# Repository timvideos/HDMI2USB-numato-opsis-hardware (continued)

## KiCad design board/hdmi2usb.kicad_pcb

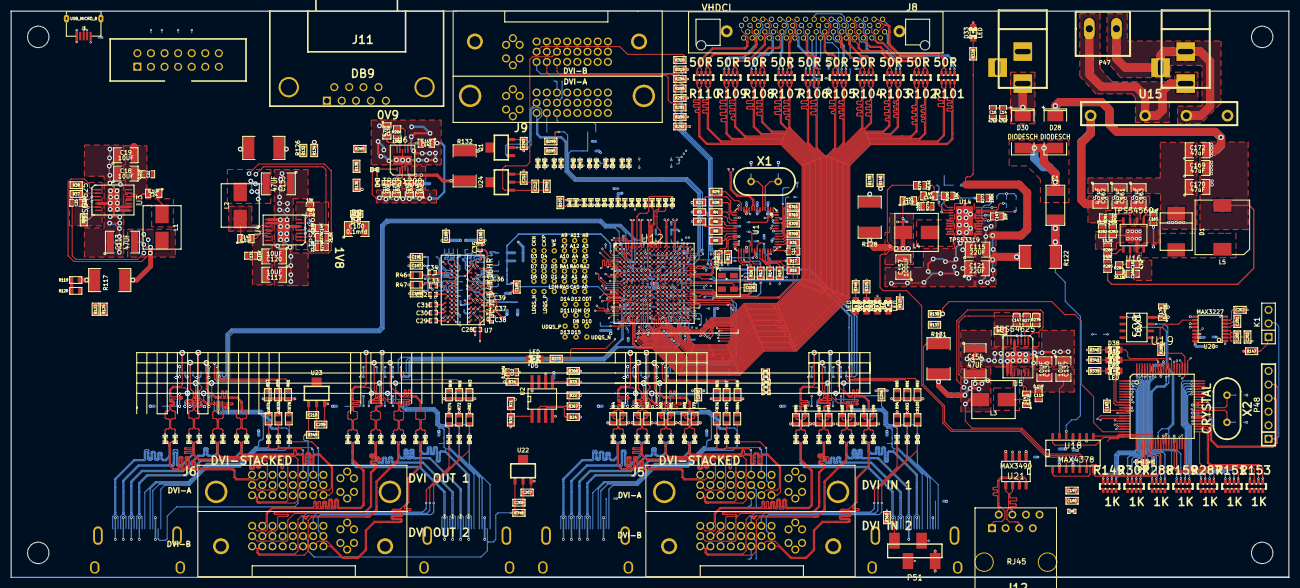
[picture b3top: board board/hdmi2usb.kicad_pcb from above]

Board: 10 copper layers, 239.0 x 105.9 mm, 688 parts (0 on the bottom side), 549 nets.

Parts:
1PIN1, 1PIN2, 1PIN3, 1PIN4: P***; MH-4MM
C1, C2, C3, C4: 0.1uFD; SM0603_Capa
C5, C6, C9, C10, C26: 0.1MFD; SM0603_Capa
C7, C8: 12pF; SM0603_Capa
C11: 47nf; SM0603_Capa
C12, C194: 0.1mfd; SM0603_Capa
C13, C15, C161, C162, C163: 4.7uF; SM1210
C14, C16: 47UF; SM0603_Capa
C17, C18, C19, C20, C116, C117, C120, C122, C125, C129, C130, C137: 10UF; SM1210
C21, C124, C133, C143: 1UF; SM0603_Capa
C22, C25, C119, C131, C144, C145, C147: 0.1UF; SM0603_Capa
C23, C132, C136: 8.2NF; SM0805
C24, C140, C141, C142, C151: 0.1UF; SM0805
C27, C48, C49, C50, C52, C53, C54, C55, C56, C58, C59, C60, C61, C62, C64, C65, C66, C67, C68, C69, C70, C71, C73, C74, C76, C77, C79, C80, C82, C83, C84, C85, C86, C87, C88, C89, C90, C91, C92, C93, C94, C95, C96, C97, C98, C99, C101, C102, C103, C104, C105, C106, C107, C108, C111, C112, C178, C181, C198: 0.1mfd; SM0402_c
C28, C29, C30, C31, C32, C33, C34, C35, C36, C37, C38, C39, C40, C41, C42, C43: 0.1mfd; SM0402_r
C44, C45, C46, C47: 1mfd; SM0603_Capa
C100: 0.1mfd; SM1210
C109: 15pf; SM0603
C110, C175, C179, C180, C182, C183, C184, C185, C186, C187, C188, C189, C190, C191, C192, C193, C195, C196, C197, C199, C200, C201, C202, C203, C204, C205, C206, C208, C210, C212: 0.1mfd; SM0603
C113, C114, C150, C153, C154, C156: 47UF; SM1812
C115, C121, C128, C134: 22UF; SM1210
C118, C123, C126, C127, C146, C148, C152, C155, C158: 10UF; SM0805
C135: 4.7UF; SM0603_Capa
C138: 0.001UF; SM0402_c
C139: 4.7UF; SM0805
C149: 1NF; SM0805
C157, C159, C160: 100UF; SM1210
C164: 2.2uF; SM1210
C165: 0.1uF; SM0603_Capa
C166: 6.2nF; SM0603_Capa
C167: 4.7uF; SM0603_Capa
C168, C169, C170, C171, C172: 47uF; SM1210
C173, C174: 0.1mfd; SM0805
C176, C177: 22pf; SM0603
C207, C209, C211: 0.33mfd; SM0603
CON1, CON2: BARREL_JACK
D1: DIODE; B560C-SMC
D2, D3, D4, D5, D32, D33, D37, D38, D39: LED; LED-0805
D28, D29, D30, D31: DIODESCH; SM2512
F1: FUSE; 1812L260THDR
GS1, GS2: GS2
J1: USB_MICRO_B; MICRO_USB_B
J2, J3, J4, J7: HDMI; HDMI_TH
J5, J6, J9: DVI-STACKED; dvi-24+5stacked
J8: VHDCI; vhdci-68
J11: DB9; DB9FC
J12: RJ45; RJ45_8
K1: CONN_3; PIN_ARRAY_3X1
L1, L2, L3: 1.5UH; IND202
L4: 2.2UH; IND202
L5: 7.2uH; Power_Inductor
P1: CONN_7X2; pin_array_7x2
P2, P3, P4, P5, P6, P7, P8, P9, P10, P11, P12, P13, P14, P15, P16, P17, P18, P19, P20, P21, P22, P23, P24, P25, P26, P27, P28, P29, P30, P31, P32, P33, P34, P35, P36, P37, P38, P39, P40, P41, P42, P43, P44, P45, P46: CONN_1; testpoint
P47: CONN_2; ScrewTerm2
P48: CONN_6; PIN_ARRAY-6X1
P51: CONN_4; PIN_ARRAY_4x1_SMD
Q1: NPN; μA78L00
R1, R2, R3, R18, R19, R20, R24, R30, R31, R34, R35, R42, R111, R133, R138, R147, R265, R292, R297, R299, R319, R324, R335, R337, R338, R344, R347, R360, R361, R362, R367, R368, R369: 10K; SM0603
R4, R5, R6, R7, R8, R9, R10, R11, R12, R13, R14, R15, R16, R17, R25, R26, R27, R29: 75R; SM0603
R21, R22, R33, R58, R60, R62, R64, R79, R81, R83, R85, R86, R87, R88, R89, R95, R97, R98, R99, R173: 50R; SM0603
R23, R28, R112, R140, R290, R293, R294, R295, R304, R328, R339, R340, R341: 2.2K; SM0603
R32, R36, R43, R57, R63, R65, R90, R348, R349, R359: 100K; SM0603
R37: 21.5K; SM0603
R38: 22.1K; SM0603
R39, R280: 10K; SM0603_Resistor
R40, R266, R272, R273, R274: 100K; SM0603_Resistor
R41: 10K; SM0402_r
R44, R45: 20K; SM0603
R46, R50, R113, R139, R141, R142, R143, R308, R310, R311, R312, R350, R351, R352, R353, R354, R355, R356, R357, R358: 100R; SM0603
R47, R49, R114, R116, R120, R134, R136, R329: 4.7K; SM0603
R48, R52, R54: 49.9R; RES_NET4
R51, R53, R55, R56, R174, R175, R176: 49.9R; SM0603
R59, R61, R66, R67, R68, R69, R91, R92, R119: 47K; SM0603
R70, R71, R72, R74, R75, R76, R93, R94, R325, R345, R346: 1.5K; SM0603
R73, R77, R80, R96: 27K; SM0603
R78, R82, R84, R100: 15K; SM0603
R101, R102, R103, R104, R105, R106, R107, R108, R109, R110: 50R; RES_NET4
R115, R137, R314, R342, R343, R370: 1K; SM0603
R117, R118, R125, R126, R127, R128, R129, R130, R131, R132: 0.03E; SM2512_N
R121, R122: 0.008E; SM2512_N
R123: 21K; SM0603
R124: 5.7K; SM0603
R135: 3.3K; SM0603
R144, R145, R146, R148, R150, R152, R154, R155, R156, R157, R158, R160, R161, R162, R163, R164, R165, R166, R167, R168, R169, R170, R171, R172, R177, R178, R179, R180, R181, R182, R183, R184, R185, R186, R187, R188, R189, R190, R191, R192, R193, R194, R195, R196, R197, R198, R199, R200, R201, R202, R203, R204, R205, R206, R207, R208, R209, R210, R211, R212, R213, R214, R215, R216, R217, R218, R219, R220, R221, R222, R223, R224, R225, R226, R227, R228, R229, R230, R231, R232, R233, R234, R235, R236, R237, R238, R239, R240, R241, R242, R243, R244, R245, R246, R247, R248, R249, R250, R251, R252, R253, R254, R255, R256, R257, R258, R259, R260, R261, R262, R263, R264, R326, R327, R331, R332, R333, R334, R336, R363: 0R; SM0402_r
R149, R151, R153, R159, R287, R288, R307: 1K; RES_NET4
R267: 200K; SM0603_Resistor
R268: 86.6K; SM0603_Resistor
R269: 1K; SM0603_Resistor
R270: 205K; SM0603_Resistor
R271: ?; SM0603_Resistor
R275: 21.5K; SM0603_Resistor
R276, R278: 22.1K; SM0603_Resistor
R277: 12.7K; SM0603_Resistor
R279: 46.4K; SM0603_Resistor
R281: 442K; SM0603_Resistor
R282: 92.3K; SM0603_Resistor
R283: 243K; SM0603_Resistor
R284: 30.1K; SM0603_Resistor
R285: 143K; SM0603_Resistor
R286: 10.2K; SM0603_Resistor
R289, R309, R313: 330R; SM0603
R291, R296, R298, R318, R323: 5.6K; SM0603
R300, R301, R302, R303, R305, R306, R315, R316, R317, R320, R321, R322: 50R; SM0402_r
R330: 0R; SM0402
U1: CY7C68013A; QFN56
U2: M25P16; SO8E_N
U3, U4, U5: TPS54625; PDSO_G14
U6: TPS51200; SON_10
U7: MT47H64M16HR; BGA84
U8, U9, U10, U11: IP4776CZ38; SSOP38
U12: SPARTAN6LXXXX-CSG324; CSG324
U13: FXO-HC536R
U14: TPS53319; DQP-22
U15: GBU15005-G; GBJ15005
U16: TPS54560
U17: MAX4377; SO8
U18: MAX4378; SO14N
U19: PIC18F85J94; TQFP-80
U20: MAX3227; SSOP17
U21: MAX3490; SO8E
U22, U23, U24: ΜA78L00; μA78L00
X1, X2: CRYSTAL; HC-49V

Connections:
/CY7C68013A/CYPRESS-RESET: C11.1, D38.2, R32.1, U1.42, U12.N14, U19.67
/CY7C68013A/DONE: R115.2, R313.2, U12.V17, U19.61
/CY7C68013A/D_N: J1.2, U1.9
/CY7C68013A/D_P: J1.3, U1.8
/CY7C68013A/INIT_B: R116.1, R289.2, U12.U3, U19.62
/CY7C68013A/PIC-OSC1: GS1.1, U1.54
/CY7C68013A/PROG_B: D39.2, R114.1, R309.2, U12.V2, U19.72
/CY7C68013A/TCK: R142.2, R312.2, U12.A17, U19.64
/CY7C68013A/TDO-USB/TDI-FPGA: R310.2, R336.2, R358.2, R363.2, U19.65
/CY7C68013A/TMS: R141.2, R311.2, U12.B18, U19.63
/CY7C68013A/U1-FD0: R4.2, U12.K12
/CY7C68013A/U1-FD1: R5.2, U12.K13
/CY7C68013A/U1-FD2: R6.2, U12.K14
/CY7C68013A/U1-FD3: R7.2, U12.J13
/CY7C68013A/U1-FD4: R8.2, U12.K16
/CY7C68013A/U1-FD5: R9.2, U12.K17
/CY7C68013A/U1-FD6: R10.2, U12.K18
/CY7C68013A/U1-FD7: R11.2, U12.L12
/CY7C68013A/U1-FIFOAD0: R14.2, U12.L13
/CY7C68013A/U1-FIFOAD1: R15.2, U12.L14
/CY7C68013A/U1-FLAGA: R27.2, U12.P16
/CY7C68013A/U1-FLAGB: R26.2, U12.L17
/CY7C68013A/U1-FLAGC: R25.2, U12.L18
/CY7C68013A/U1-IFCLK: R29.1, U12.P15
/CY7C68013A/U1-INT0#: R12.2, U12.M14
/CY7C68013A/U1-PKTEND: R16.2, U12.M16
/CY7C68013A/U1-SCL: R23.1, U1.15
/CY7C68013A/U1-SDA: R28.1, U1.16
/CY7C68013A/U1-SLCS: R17.2, U12.M18
/CY7C68013A/U1-SLRD: R20.2, U1.1, U12.J18
/CY7C68013A/U1-SLWR: R19.2, U1.2, U12.M13
/MT47H64M16HR/DDR-A0: P35.1, R175.2, U7.M8, U12.J7
/MT47H64M16HR/DDR-A1: P34.1, R174.2, U7.M3, U12.J6
/MT47H64M16HR/DDR-A2: P33.1, R176.2, U7.M7, U12.H5
/MT47H64M16HR/DDR-A3: P32.1, R52.5, U7.N2, U12.L7
/MT47H64M16HR/DDR-A4: P31.1, R48.1, U7.N8, U12.F3
/MT47H64M16HR/DDR-A5: P30.1, R52.1, U7.N3, U12.H4
/MT47H64M16HR/DDR-A6: P29.1, R48.7, U7.N7, U12.H3
/MT47H64M16HR/DDR-A7: P28.1, R52.7, U7.P2, U12.H6
/MT47H64M16HR/DDR-A8: P27.1, R48.3, U7.P8, U12.D2
/MT47H64M16HR/DDR-A9: P26.1, R52.3, U7.P3, U12.D1
/MT47H64M16HR/DDR-A10: P25.1, R53.2, U7.M2, U12.F4
/MT47H64M16HR/DDR-A11: P24.1, R48.5, U7.P7, U12.D3
/MT47H64M16HR/DDR-A12: P23.1, R51.2, U7.R2, U12.G6
/MT47H64M16HR/DDR-BA0: P22.1, R54.4, U7.L2, U12.F2
/MT47H64M16HR/DDR-BA1: P37.1, R54.8, U7.L3, U12.F1
/MT47H64M16HR/DDR-BA2: P39.1, R54.6, U7.L1, U12.E1
/MT47H64M16HR/DDR-CAS: P42.1, R55.1, U7.L7, U12.K5
/MT47H64M16HR/DDR-CKE: P38.1, R49.1, U7.K2, U12.H7
/MT47H64M16HR/DDR-CK_N: P36.1, R50.1, U7.K8, U12.G1
/MT47H64M16HR/DDR-CK_P: P21.1, R50.2, U7.J8, U12.G3
/MT47H64M16HR/DDR-D0: P17.1, U7.G8, U12.L2
/MT47H64M16HR/DDR-D1: P16.1, U7.G2, U12.L1
/MT47H64M16HR/DDR-D2: P15.1, U7.H7, U12.K2
/MT47H64M16HR/DDR-D3: P14.1, U7.H3, U12.K1
/MT47H64M16HR/DDR-D4: P13.1, U7.H1, U12.H2
/MT47H64M16HR/DDR-D5: P12.1, U7.H9, U12.H1
/MT47H64M16HR/DDR-D6: P11.1, U7.F1, U12.J3
/MT47H64M16HR/DDR-D7: P10.1, U7.F9, U12.J1
/MT47H64M16HR/DDR-D8: P9.1, U7.C8, U12.M3
/MT47H64M16HR/DDR-D9: P8.1, U7.C2, U12.M1
/MT47H64M16HR/DDR-D10: P7.1, U7.D7, U12.N2
/MT47H64M16HR/DDR-D11: P6.1, U7.D3, U12.N1
/MT47H64M16HR/DDR-D12: P5.1, U7.D1, U12.T2
/MT47H64M16HR/DDR-D13: P4.1, U7.D9, U12.T1
/MT47H64M16HR/DDR-D14: P3.1, U7.B1, U12.U2
/MT47H64M16HR/DDR-D15: P2.1, U7.B9, U12.U1
/MT47H64M16HR/DDR-LDM: P19.1, U7.F3, U12.K3
/MT47H64M16HR/DDR-LDQS_N: P44.1, U7.E8, U12.L3
/MT47H64M16HR/DDR-LDQS_P: P46.1, U7.F7, U12.L4
/MT47H64M16HR/DDR-ODT: P18.1, R47.1, U7.K9, U12.K6
/MT47H64M16HR/DDR-RAS: P41.1, R56.1, U7.K7, U12.L5
/MT47H64M16HR/DDR-UDM: P20.1, U7.B3, U12.K4
/MT47H64M16HR/DDR-UDQS_N: P45.1, U7.A8, U12.P1
/MT47H64M16HR/DDR-UDQS_P: P43.1, U7.B7, U12.P2
/MT47H64M16HR/DDR-WE: P40.1, R54.2, U7.K3, U12.E3
/expansion connectors/EXP-IO1_N: J8.35, R101.3, R101.4, U12.V5
/expansion connectors/EXP-IO1_P: J8.1, R101.1, R101.2, U12.U5
/expansion connectors/EXP-IO2_N: J8.37, R101.7, R101.8, U12.V6
/expansion connectors/EXP-IO2_P: J8.3, R101.5, R101.6, U12.T6
/expansion connectors/EXP-IO3_N: J8.38, R102.3, R102.4, U12.P7
/expansion connectors/EXP-IO3_P: J8.4, R102.1, R102.2, U12.N6
/expansion connectors/EXP-IO4_N: J8.40, R102.7, R102.8, U12.T7
/expansion connectors/EXP-IO4_P: J8.6, R102.5, R102.6, U12.R7
/expansion connectors/EXP-IO5_N: J8.41, R103.3, R103.4, U12.V7
/expansion connectors/EXP-IO5_P: J8.7, R103.1, R103.2, U12.U7
/expansion connectors/EXP-IO6_N: J8.43, R103.7, R103.8, U12.T8
/expansion connectors/EXP-IO6_P: J8.9, R103.5, R103.6, U12.R8
/expansion connectors/EXP-IO7_N: J8.44, R104.3, R104.4, U12.P8
/expansion connectors/EXP-IO7_P: J8.10, R104.1, R104.2, U12.N7
/expansion connectors/EXP-IO8_N: J8.46, R104.7, R104.8, U12.V8
/expansion connectors/EXP-IO8_P: J8.12, R104.5, R104.6, U12.U8
/expansion connectors/EXP-IO9_N: J8.47, R105.3, R105.4, U12.N8
/expansion connectors/EXP-IO9_P: J8.13, R105.1, R105.2, U12.M8
/expansion connectors/EXP-IO10_N: J8.49, R105.7, R105.8, U12.N9
/expansion connectors/EXP-IO10_P: J8.15, R105.5, R105.6, U12.M10
/expansion connectors/EXP-IO11_N: J8.54, R106.3, R106.4, U12.V10
/expansion connectors/EXP-IO11_P: J8.20, R106.1, R106.2, U12.U10
/expansion connectors/EXP-IO12_N: J8.56, R106.7, R106.8, U12.N11
/expansion connectors/EXP-IO12_P: J8.22, R106.5, R106.6, U12.M11
/expansion connectors/EXP-IO13_N: J8.57, R107.3, R107.4, U12.V11
/expansion connectors/EXP-IO13_P: J8.23, R107.1, R107.2, U12.U11
/expansion connectors/EXP-IO14_N: J8.59, R107.7, R107.8, U12.P11
/expansion connectors/EXP-IO14_P: J8.25, R107.5, R107.6, U12.N10
/expansion connectors/EXP-IO15_N: J8.60, R108.3, R108.4, U12.T11
/expansion connectors/EXP-IO15_P: J8.26, R108.1, R108.2, U12.R11
/expansion connectors/EXP-IO16_N: J8.62, R108.7, R108.8, U12.P12
/expansion connectors/EXP-IO16_P: J8.28, R108.5, R108.6, R112.2, U12.N12
/expansion connectors/EXP-IO17_N: J8.63, R109.3, R109.4, U12.T10
/expansion connectors/EXP-IO17_P: J8.29, R109.1, R109.2, U12.R10
/expansion connectors/EXP-IO18_N: J8.65, R109.7, R109.8, U12.V12
/expansion connectors/EXP-IO18_P: J8.31, R109.5, R109.6, U12.T12
/expansion connectors/EXP-IO19_N: J8.66, R110.3, R110.4, U12.V13
/expansion connectors/EXP-IO19_P: J8.32, R110.1, R110.2, U12.U13
/expansion connectors/EXP-IO20_N: J8.68, R110.7, R110.8, U12.V15
/expansion connectors/EXP-IO20_P: J8.34, R110.5, R110.6, U12.U15
/expansion connectors/GTP-RX-0_N: J9.A17, R315.2, U12.C5
/expansion connectors/GTP-RX-0_P: J9.A18, R305.2, R334.2
/expansion connectors/GTP-RX-1_N: J9.A9, R320.1, U12.C7
/expansion connectors/GTP-RX-1_P: J9.A10, R322.1, R332.2
/expansion connectors/GTP-RX-2_N: J9.A1, R301.1, U12.C11
/expansion connectors/GTP-RX-2_P: J9.A2, R303.1, U12.D11
/expansion connectors/GTP-RX-3_N: J9.A12, R321.2, U12.C13
/expansion connectors/GTP-RX-3_P: J9.A13, R317.2, R333.2
/expansion connectors/GTP-RX-CLK_N: J9.A24, R300.2, U12.A10
/expansion connectors/GTP-RX-CLK_P: J9.A23, R302.2, R331.2
/expansion connectors/GTP-RX-ECLK_N: J9.A4, R306.1, U12.C9
/expansion connectors/GTP-RX-ECLK_P: J9.A5, R316.1, U12.D9
/expansion connectors/GTP-RX-HOT: Q1.2, U12.F14
/expansion connectors/GTP-RX-SCL: R304.1, R323.1, R324.2, U12.C17
/expansion connectors/GTP-RX-SDA: R295.1, R298.1, R299.2, U12.C18
/expansion connectors/GTP-RX-VIO: J9.A8, U12.D17
/expansion connectors/GTP-RX_HOT: J9.A16, Q1.1
/expansion connectors/GTP-RX_SCL: J9.A6, R323.2
/expansion connectors/GTP-RX_SDA: J9.A7, R298.2
/expansion connectors/GTP-TX-0_N: J9.B17, U12.A6
/expansion connectors/GTP-TX-0_P: J9.B18, U12.B6
/expansion connectors/GTP-TX-1_N: J9.B9, U12.A4
/expansion connectors/GTP-TX-1_P: J9.B10, U12.B4
/expansion connectors/GTP-TX-2_N: J9.B1, U12.A12
/expansion connectors/GTP-TX-2_P: J9.B2, U12.B12
/expansion connectors/GTP-TX-3_N: J9.B12, U12.A14
/expansion connectors/GTP-TX-3_P: J9.B13, U12.B14
/expansion connectors/GTP-TX-CLK_N: J9.B24, U12.B8, U12.E18
/expansion connectors/GTP-TX-CLK_P: J9.B23, U12.A8, U12.E16
/expansion connectors/GTP-TX-ECLK_N: J9.B4, R330.2
/expansion connectors/GTP-TX-ECLK_P: J9.B5, U12.F10
/expansion connectors/GTP-TX-HOT: R318.1, R319.2, U12.H17
/expansion connectors/GTP-TX-SCL: R294.1, R296.1, R297.2, U12.G13
/expansion connectors/GTP-TX-SDA: R290.1, R291.1, R292.2, U12.G14
/expansion connectors/GTP-TX-VCC5V0: C212.1, J9.B14, R359.2, U24.1
/expansion connectors/GTP-TX-VIO: J9.B8, U12.G18
/expansion connectors/GTP-TX_HOT: J9.B16, R318.2
/expansion connectors/GTP-TX_SCL: J9.B6, R296.2
/expansion connectors/GTP-TX_SDA: J9.B7, R291.2
/expansion connectors/TDO-FPGA/TDO-JTAG: R143.2, R308.2, U12.D16, U19.66
/hdmi/HDMI-TX1-VCC5V0: C208.1, J3.18, J6.B14, R348.1, U22.1
/hdmi/HDMI-TX2-VCC5V0: C210.1, J2.18, J6.A14, R349.1, U23.1
/hdmi/P1-CEC: J4.13, R80.2, U10.23
/hdmi/P1-HOT: C205.2, R84.2, R187.1, R205.1, R342.2, U10.20
/hdmi/P1-SCL: R76.2, R185.1, R201.1, U10.22
/hdmi/P1-SDA: R75.2, R186.1, R202.1, U10.21
/hdmi/P2-CEC: J3.13, R77.2, U9.23
/hdmi/P2-HOT: R82.2, R198.1, R216.1, U9.20
/hdmi/P2-SCL: R74.2, R196.1, R212.1, U9.22
/hdmi/P2-SDA: R72.2, R197.1, R213.1, U9.21
/hdmi/P3-CEC: J7.13, R96.2, U11.23
/hdmi/P3-HOT: C206.2, R100.2, R227.1, R242.1, R343.2, U11.20
/hdmi/P3-SCL: R94.2, R223.1, R240.1, U11.22
/hdmi/P3-SDA: R93.2, R224.1, R241.1, U11.21
/hdmi/P4-CEC: J2.13, R73.2, U8.23
/hdmi/P4-HOT: R78.2, R249.1, R264.1, U8.20
/hdmi/P4-SCL: R71.2, R245.1, R262.1, U8.22
/hdmi/P4-SDA: R70.2, R246.1, R263.1, U8.21
/hdmi/TMDS-RX1-0_N: R81.1, R182.1, R206.1, U10.27, U12.T18
/hdmi/TMDS-RX1-0_P: R60.1, R181.1, R207.1, U10.10, U12.T17
/hdmi/TMDS-RX1-1_N: R83.1, R180.1, R203.1, U10.30, U12.N16
/hdmi/TMDS-RX1-1_P: R62.1, R179.1, R204.1, U10.7, U12.N15
/hdmi/TMDS-RX1-2_N: R85.1, R178.1, R199.1, U10.33, U12.U18
/hdmi/TMDS-RX1-2_P: R64.1, R177.1, R200.1, U10.4, U12.U17
/hdmi/TMDS-RX1-CEC: R65.2, U10.16, U12.P18
/hdmi/TMDS-RX1-CLK_N: R79.1, R184.1, R209.1, U10.24, U12.L16
/hdmi/TMDS-RX1-CLK_P: R58.1, R183.1, R208.1, U10.13, U12.L15
/hdmi/TMDS-RX1-HOT: U10.19, U12.N18
/hdmi/TMDS-RX1-SCL: R67.2, U10.17, U12.N17
/hdmi/TMDS-RX1-SDA: R69.2, U10.18, U12.P17
/hdmi/TMDS-RX2-0_N: R98.2, R228.1, R237.1, U11.27, U12.F18
/hdmi/TMDS-RX2-0_P: R88.1, R229.1, R236.1, U11.10, U12.F17
/hdmi/TMDS-RX2-1_N: R97.2, R225.1, R235.1, U11.30, U12.F16
/hdmi/TMDS-RX2-1_P: R87.1, R226.1, R234.1, U11.7, U12.F15
/hdmi/TMDS-RX2-2_N: R95.2, R221.1, R233.1, U11.33, U12.H14
/hdmi/TMDS-RX2-2_P: R86.1, R222.1, R232.1, U11.4, U12.H13
/hdmi/TMDS-RX2-CEC: R90.2, U11.16, U12.G16
/hdmi/TMDS-RX2-CLK_N: R99.2, R231.1, R239.1, U11.24, U12.H16
/hdmi/TMDS-RX2-CLK_P: R89.1, R230.1, R238.1, U11.13, U12.H15
/hdmi/TMDS-RX2-HOT: U11.19, U12.D18
/hdmi/TMDS-RX2-SCL: R91.2, U11.17, U12.H18
/hdmi/TMDS-RX2-SDA: R92.2, U11.18, U12.H12
/hdmi/TMDS-TX1-0_N: R193.1, R217.1, U9.27, U12.T3
/hdmi/TMDS-TX1-0_P: R192.1, R218.1, U9.10, U12.R3
/hdmi/TMDS-TX1-1_N: R191.1, R214.1, U9.30, U12.V4
/hdmi/TMDS-TX1-1_P: R190.1, R215.1, U9.7, U12.T4
/hdmi/TMDS-TX1-2_N: R189.1, R210.1, U9.33, U12.T5
/hdmi/TMDS-TX1-2_P: R188.1, R211.1, U9.4, U12.R5
/hdmi/TMDS-TX1-CEC: R63.2, U9.16, U12.P6
/hdmi/TMDS-TX1-CLK_N: R195.1, R220.1, U9.24, U12.V9
/hdmi/TMDS-TX1-CLK_P: R194.1, R219.1, U9.13, U12.T9
/hdmi/TMDS-TX1-HOT: U9.19, U12.N5
/hdmi/TMDS-TX1-SCL: R66.2, U9.17, U12.V16
/hdmi/TMDS-TX1-SDA: R68.2, U9.18, U12.U16
/hdmi/TMDS-TX2-0_N: R250.1, R259.1, U8.27, U12.A16
/hdmi/TMDS-TX2-0_P: R251.1, R258.1, U8.10, U12.B16
/hdmi/TMDS-TX2-1_N: R247.1, R257.1, U8.30, U12.A3
/hdmi/TMDS-TX2-1_P: R248.1, R256.1, U8.7, U12.B3
/hdmi/TMDS-TX2-2_N: R243.1, R255.1, U8.33, U12.A2
/hdmi/TMDS-TX2-2_P: R244.1, R254.1, U8.4, U12.B2
/hdmi/TMDS-TX2-CEC: R57.2, U8.16, U12.E4
/hdmi/TMDS-TX2-CLK_N: R253.1, R261.1, U8.24, U12.A15
/hdmi/TMDS-TX2-CLK_P: R252.1, R260.1, U8.13, U12.C15
/hdmi/TMDS-TX2-HOT: U8.19, U12.G9
/hdmi/TMDS-TX2-SCL: R59.2, U8.17, U12.F6
/hdmi/TMDS-TX2-SDA: R61.2, U8.18, U12.F5
/pmic/232-FON: U19.8, U20.12
/pmic/232-INV: U19.10, U20.10
/pmic/232-RDY: U19.5, U20.1
/pmic/CURRENT_0V9: U17.7, U19.33
/pmic/CURRENT_1V2: U18.7, U19.30
/pmic/CURRENT_1V8: U17.1, U19.29
/pmic/CURRENT_3V3: U18.1, U19.28
/pmic/CURRENT_5V0: U18.8, U19.27
/pmic/CURRENT_12V0: U18.14, U19.22
/pmic/DDR0V9_RS+: C146.2, C148.2, C152.2, C155.2, C158.2, R127.2, R132.2, U6.3, U6.5, U17.5
/pmic/DDR1V8_RS+: C145.2, C150.2, C153.2, L2.2, R125.2, R126.2, R275.1, U4.1, U17.3
/pmic/IR-LED: R140.1, U19.54
/pmic/L-GRX-A: R149.7, U19.1
/pmic/L-GRX-D: R307.3, U19.79
/pmic/L-GRX-E: R149.5, U19.2
/pmic/L-GRX-M: R307.1, U19.80
/pmic/L-GTX-A: R151.3, U19.56
/pmic/L-GTX-D: R287.1, U19.58
/pmic/L-GTX-E: R151.5, U19.55
/pmic/L-GTX-M: R151.1, U19.57
/pmic/L-PGOOD: R287.3, U19.34
/pmic/L-RX1-A: R159.3, U19.68
/pmic/L-RX1-C: R149.1, U19.4
/pmic/L-RX1-D: R288.1, U19.76
/pmic/L-RX1-E: R151.7, U19.39
/pmic/L-RX2-A: R159.5, U19.60
/pmic/L-RX2-C: R307.5, U19.78
/pmic/L-RX2-D: R288.5, U19.74
/pmic/L-RX2-E: R153.3, U19.41
/pmic/L-TX1-A: R159.1, U19.69
/pmic/L-TX1-C: R149.3, U19.3
/pmic/L-TX1-D: R288.3, U19.75
/pmic/L-TX1-E: R153.1, U19.40
/pmic/L-TX2-A: R159.7, U19.59
/pmic/L-TX2-C: R307.7, U19.77
/pmic/L-TX2-D: R288.7, U19.73
/pmic/L-TX2-E: R153.5, U19.42
/pmic/L-V-A: R287.5, U19.35
/pmic/L-V-D: R287.7, U19.36
/pmic/L-V-E: R153.7, U19.43
/pmic/OSC1: C176.2, GS1.2, U19.49, X2.2
/pmic/OSC2: C177.2, U19.50, X2.1
/pmic/PIC-RESET: C204.1, D37.2, K1.2, P48.1, U12.T14, U19.9
/pmic/RS232RX: U19.6, U20.9
/pmic/RS232RX-IN: J11.3, U20.8
/pmic/RS232TX: U19.7, U20.11
/pmic/RS232TX-OUT: J11.2, U20.13
/pmic/RS422RX: U19.37, U21.2
/pmic/RS422RX-IN+: J12.2, U21.8
/pmic/RS422RX-IN-: J12.1, U21.7
/pmic/RS422TX: U19.38, U21.3
/pmic/RS422TX-IN+: J12.5, U21.5
/pmic/RS422TX-IN-: J12.4, U21.6
/pmic/SPI-CS-PIC: U12.V14, U19.13
/pmic/SPI-SCK: P48.5, R369.1, U2.6, U12.R15, U19.44, U19.52
/pmic/SPI-SDI: R22.1, U12.R13, U19.45
/pmic/SPI-SDO: P48.4, R33.2, U12.T13, U19.46, U19.47
/pmic/USB_DM: P51.2, U19.17
/pmic/USB_DP: P51.3, U19.16
/pmic/VCC3V3_RS+: C151.1, C157.2, C159.2, C160.2, L4.2, R128.2, R129.2, R279.2, U18.3
/pmic/VCC5V0_RS+: C25.2, C113.2, C114.2, L1.2, R37.1, R117.2, R118.2, U3.1, U18.10
/pmic/VCC12V0_RS+: F1.2, R121.2, R122.2, U18.12
/pmic/VSENSE_0V9: R139.2, U19.21
/pmic/VSENSE_1V2: R137.2, R138.1, U19.20
/pmic/VSENSE_1V8: R135.2, R136.1, U19.19
/pmic/VSENSE_3V3: R133.2, R134.1, U19.18
/pmic/VSENSE_5V0: R123.2, R124.1, U19.15
/pmic/VSENSE_12V0: R119.2, R120.1, U19.14
/power/Conference 12V: C168.2, C169.2, C170.2, C171.2, C172.2, D28.1, D29.1, L5.2, R285.2
/power/Consumer 12V: C14.2, C16.2, CON2.1, D30.1, D31.1
/power/VCC1V2_RS+: C147.1, C154.2, C156.2, L3.2, R130.2, R131.2, R137.1, R277.1, U5.1, U18.6
/power/VIN 48: C13.2, C15.2, C161.2, C162.2, C163.2, C164.2, R281.2, U15.1, U16.2
/power/VIN +48V: CON1.1, P47.2, U15.2
/power/VIN -48V: CON1.2, CON1.3, P47.1, U15.3
/spartan6/CMPCS_B_2: R314.1, U12.P13
/spartan6/GCLK: C109.1, U12.K15, U13.3
/spartan6/GND--OR--VCC1V2-1: R156.1, R157.1, U12.D10
/spartan6/GNDT-NC1: R169.1, U12.C4
/spartan6/GNDT-NC2: R170.1, U12.C6
/spartan6/GNDT-NC3: R171.1, U12.A7
/spartan6/GNDT-NC4: R172.1, U12.D8
/spartan6/GNDT-NC5: R160.1, U12.B9
/spartan6/GNDT-NC6: R161.1, U12.A9
/spartan6/GNDT-NC7: R162.1, U12.C10
/spartan6/GNDT-NC8: R163.1, U12.F9
/spartan6/GNDT-NC9: R164.1, U12.A11
/spartan6/GNDT-NC10: R165.1, U12.E13
/spartan6/GNDT-NC11: R167.1, U12.C14
/spartan6/GTP-REF: R173.1, U12.E7
/spartan6/GTP-RX-0_P--OR--GND: R158.1, R334.1, U12.D5
/spartan6/GTP-RX-1_P--OR--VCC3V3: R150.1, R332.1, U12.D7
/spartan6/GTP-RX-3_P--OR--VCC3V3: R152.1, R333.1, U12.D13
/spartan6/GTP-RX-CLK_P--OR--VCC3V3: R148.1, R331.1, U12.B10
/spartan6/GTP-TX-ECLK_N--OR--VCC3V3: R146.1, R330.1, U12.E10
/spartan6/GTP_CAL: R173.2, R326.1, R327.1, U12.E5
/spartan6/LED-DEBUG: R370.2, U12.P3
/spartan6/M0: GS2.1, R111.2, U12.T15
/spartan6/NC-VCCAUXT1: R168.1, U12.D4
/spartan6/NC-VCCAUXT2: R166.1, U12.D14
/spartan6/RZQ: R113.2, U12.L6
/spartan6/SPI-CS-FLASH: R21.1, U12.V3
/spartan6/SUSPEND: R329.2, U12.R16
/spartan6/TDO_USB/TDI-FPGA-LX: R336.1, U12.D15
/spartan6/TDO_USB/TDI-FPGA-LXT: R363.1, U12.F13
/spartan6/U1-SLOE: R13.2, U12.J16
/spartan6/VCC3V3--OR--GND1: R144.1, R145.1, U12.B5
/spartan6/VCC3V3--OR--VCC1V2: R154.1, R155.1, U12.E9
DDR0V9: C27.1, C111.1, C112.1, C184.1, C185.1, C186.1, C187.1, C188.1, C189.1, C190.1, C191.1, C192.1, C193.1, R48.2, R48.4, R48.6, R48.8, R51.1, R52.2, R52.4, R52.6, R52.8, R53.1, R54.1, R54.3, R54.5, R54.7, R55.2, R56.2, R127.1, R132.1, R139.1, R174.1, R175.1, R176.1, U12.C1, U12.M5, U12.N3, U17.6
DDR1V8: C28.1, C29.1, C30.1, C31.1, C32.1, C33.1, C34.1, C35.1, C36.1, C37.1, C38.1, C39.1, C40.1, C41.1, C42.1, C43.1, C86.1, C89.1, C92.1, C95.1, C98.1, C101.1, C118.2, C123.2, C126.1, C127.2, R41.1, R44.1, R125.1, R126.1, R135.1, U6.2, U7.A1, U7.A9, U7.C1, U7.C3, U7.C7, U7.C9, U7.E1, U7.E9, U7.G1, U7.G3, U7.G7, U7.G9, U7.J1, U7.J9, U7.M9, U7.R1, U12.E2, U12.G4, U12.J2, U12.J5, U12.M4, U12.R2, U17.2
GND: C1.2, C2.2, C3.2, C4.2, C5.2, C6.2, C7.1, C8.2, C9.2, C10.2, C11.2, C12.2, C13.1, C14.1, C15.1, C16.1, C17.2, C18.1, C19.1, C20.2, C21.1, C22.2, C23.1, C26.2, C27.2, C28.2, C29.2, C30.2, C31.2, C32.2, C33.2, C34.2, C35.2, C36.2, C37.2, C38.2, C39.2, C40.2, C41.2, C42.2, C43.2, C44.2, C45.2, C46.2, C47.2, C48.2, C49.2, C50.2, C52.2, C53.2, C54.2, C55.2, C56.2, C58.2, C59.2, C60.2, C61.2, C62.2, C64.2, C65.2, C66.2, C67.2, C68.2, C69.2, C70.2, C71.2, C73.2, C74.2, C76.2, C77.2, C79.2, C80.2, C82.2, C83.2, C84.2, C85.2, C86.2, C87.2, C88.2, C89.2, C90.2, C91.2, C92.2, C93.2, C94.2, C95.2, C96.2, C97.2, C98.2, C99.2, C100.2, C101.2, C102.2, C103.2, C104.2, C105.2, C106.2, C107.2, C108.2, C109.2, C110.2, C111.2, C112.2, C113.1, C114.1, C115.1, C116.2, C117.1, C118.1, C119.2, C120.1, C121.1, C122.2, C123.1, C124.1, C125.1, C126.2, C127.1, C128.1, C129.1, C130.1, C131.2, C132.1, C133.1, C134.1, C135.1, C136.1, C137.1, C138.2, C139.1, C142.1, C143.1, C146.1, C148.1, C150.1, C152.1, C153.1, C154.1, C155.1, C156.1, C157.1, C158.1, C159.1, C160.1, C161.1, C162.1, C163.1, C164.1, C166.2, C167.1, C168.1, C169.1, C170.1, C171.1, C172.1, C173.2, C174.2, C175.2, C176.1, C177.1, C178.2, C179.2, C180.2, C181.2, C182.2, C183.1, C184.2, C185.2, C186.2, C187.2, C188.2, C189.2, C190.2, C191.2, C192.2, C193.2, C194.2, C195.2, C196.2, C197.2, C198.2, C199.2, C202.1, C203.1, C204.2, C205.1, C206.1, CON2.2, CON2.3, D1.1, D3.2, D4.2, D5.2, D32.2, D33.2, GS2.2, J1.5, J2.2, J2.5, J2.8, J2.11, J2.17, J3.2, J3.5, J3.8, J3.11, J3.17, J4.2, J4.5, J4.8, J4.11, J4.17, J5.A3, J5.A11, J5.A15, J5.A19, J5.A22, J5.B3, J5.B11, J5.B15, J5.B19, J5.B22, J6.A3, J6.A11, J6.A15, J6.A19, J6.A22, J6.B3, J6.B11, J6.B15, J6.B19, J6.B22, J7.2, J7.5, J7.8, J7.11, J7.17, J8.2, J8.5, J8.8, J8.11, J8.14, J8.21, J8.24, J8.27, J8.30, J8.33, J8.36, J8.39, J8.42, J8.45, J8.48, J8.55, J8.58, J8.61, J8.64, J8.67, J9.A3, J9.A11, J9.A15, J9.A19, J9.A22, J9.B3, J9.B11, J9.B15, J9.B19, J9.B22, J11.5, J12.3, J12.6, K1.3, P1.1, P1.3, P1.5, P1.7, P1.9, P1.11, P1.13, P48.3, P51.1, R18.1, R38.2, R45.1, R46.2, R47.2, R49.2, R78.1, R82.1, R84.1, R100.1, R112.1, R113.1, R120.2, R124.2, R134.2, R136.2, R138.2, R145.2, R156.2, R158.2, R160.2, R161.2, R162.2, R163.2, R164.2, R165.2, R167.2, R169.2, R170.2, R171.2, R172.2, R265.2, R268.2, R270.2, R271.2, R272.1, R276.2, R278.2, R280.1, R282.2, R283.2, R286.1, R292.1, R297.1, R299.1, R319.1, R324.1, R329.1, R335.1, R337.1, R338.1, R344.1, R347.1, R360.2, R361.1, R362.1, U1.6, U1.10, U1.12, U1.14, U1.26, U1.28, U1.41, U1.53, U1.56, U2.4, U3.5, U3.8, U3.9, U3.15, U4.5, U4.8, U4.9, U4.15, U5.5, U5.8, U5.9, U5.15, U6.4, U6.8, U6.11, U7.A3, U7.A7, U7.B2, U7.B8, U7.D2, U7.D8, U7.E3, U7.E7, U7.F2, U7.F8, U7.H2, U7.H8, U7.J3, U7.J7, U7.N1, U7.P9, U8.3, U8.5, U8.8, U8.11, U8.14, U8.25, U8.28, U8.31, U8.34, U8.36, U9.3, U9.5, U9.8, U9.11, U9.14, U9.25, U9.28, U9.31, U9.34, U9.36, U10.3, U10.5, U10.8, U10.11, U10.14, U10.25, U10.28, U10.31, U10.34, U10.36, U11.3, U11.5, U11.8, U11.11, U11.14, U11.25, U11.28, U11.31, U11.34, U11.36, U12.A1, U12.A18, U12.B13, U12.C12, U12.C16, U12.E15, U12.F11, U12.G2, U12.G5, U12.G17, U12.H8, U12.H10, U12.J4, U12.J9, U12.J11, U12.J15, U12.K8, U12.K10, U12.L9, U12.L11, U12.M2, U12.M6, U12.M17, U12.N13, U12.R1, U12.R4, U12.R9, U12.R14, U12.R18, U12.T16, U12.U6, U12.U12, U12.V1, U12.V18, U13.2, U14.23, U15.4, U16.7, U16.9, U17.4, U18.11, U19.11, U19.26, U19.31, U19.51, U19.70, U20.14, U21.4
unnamed: K1.1, R147.1
unnamed: D2.2, R115.1
unnamed: R34.1, U2.7
unnamed: R21.2, R30.1, U2.1
unnamed: R24.2, U2.3
unnamed: R22.2, R367.2, U2.2
unnamed: R33.1, R368.1, U2.5
unnamed: D5.1, R370.1
unnamed: R3.2, R13.1, U1.35
unnamed: R1.2, R12.1, U1.33
unnamed: R31.2, U1.44
unnamed: R10.1, U1.24
unnamed: R310.1, U1.47
unnamed: R29.2, U1.13
unnamed: R289.1, U1.51
unnamed: R6.1, U1.20
unnamed: R7.1, U1.21
unnamed: R8.1, U1.22
unnamed: R9.1, U1.23
unnamed: R11.1, U1.25
unnamed: R4.1, U1.18
unnamed: R5.1, U1.19
unnamed: R17.1, R18.2, U1.40
unnamed: C7.2, U1.4, X1.2
unnamed: C8.1, U1.5, X1.1
unnamed: R25.1, U1.31
unnamed: R26.1, U1.30
unnamed: R27.1, U1.29
unnamed: R344.2, R346.2, U1.36
unnamed: R14.1, U1.37
unnamed: R16.1, U1.39
unnamed: J1.1, R347.2
unnamed: R308.1, U1.45
unnamed: R311.1, U1.48
unnamed: R312.1, U1.49
unnamed: R309.1, U1.46
unnamed: R313.1, U1.52
unnamed: D3.1, R345.1
unnamed: D4.1, R346.1
unnamed: R2.2, R345.2, U1.34
unnamed: R325.1, U1.50
unnamed: D32.1, R325.2
unnamed: R15.1, U1.38
unnamed: C26.1, R44.2, R45.2, U7.J2
unnamed: R46.1, U7.L8
unnamed: R269.1, U14.2
unnamed: R267.2, R268.1, R269.2
unnamed: C24.1, L1.1, U3.10, U3.11
unnamed: C24.2, U3.12
unnamed: R271.1, U14.22
unnamed: R270.1, U14.21
unnamed: C144.1, U14.4
unnamed: R272.2, U14.20
unnamed: R273.2, U14.3
unnamed: C143.2, R273.1, U14.18
unnamed: C144.2, L4.1, R274.2, U14.6, U14.7, U14.8, U14.9, U14.10, U14.11
unnamed: R266.1, U6.9
unnamed: C149.1, R279.1, R280.2, U14.1
unnamed: C138.1, R41.2, R265.1, U6.1
unnamed: C142.2, U6.6
unnamed: D28.2, D29.2, D30.2, D31.2, F1.1
unnamed: D33.1, R328.2
unnamed: C25.1, R37.2, R38.1, U3.2
unnamed: R35.2, U3.7
unnamed: R36.2, U3.6
unnamed: C23.2, U3.4
unnamed: C166.1, R284.1
unnamed: R285.1, R286.2, U16.5
unnamed: C165.2, D1.2, L5.1, U16.8
unnamed: C165.1, U16.1
unnamed: R283.1, U16.4
unnamed: R281.1, R282.1, U16.3
unnamed: C149.2, C151.2, R274.1
unnamed: C21.2, R36.1, U3.3
unnamed: C141.2, U5.12
unnamed: C141.1, L3.1, U5.10, U5.11
unnamed: C136.2, U5.4
unnamed: C147.2, R277.2, R278.1, U5.2
unnamed: C133.2, R43.1, U5.3
unnamed: R43.2, U5.6
unnamed: C140.2, U4.12
unnamed: C140.1, L2.1, U4.10, U4.11
unnamed: C132.2, U4.4
unnamed: C124.2, R40.1, U4.3
unnamed: R40.2, U4.6
unnamed: R39.2, U4.7
unnamed: R42.2, U5.7
unnamed: C145.1, R275.2, R276.1, U4.2
unnamed: C167.2, R284.2, U16.6
unnamed: J5.B14, R362.2
unnamed: J4.18, R337.2
unnamed: J5.A14, R361.2
unnamed: C46.1, U9.37
unnamed: C209.2, C210.2, R349.2, U23.2
unnamed: C207.2, C208.2, R348.2, U22.2
unnamed: J2.1, R254.2
unnamed: J2.9, R259.2
unnamed: J2.7, R258.2
unnamed: J2.6, R257.2
unnamed: J2.4, R256.2
unnamed: J2.3, R255.2
unnamed: J2.10, R260.2
unnamed: J7.19, R242.2
unnamed: J7.16, R241.2
unnamed: J7.15, R240.2
unnamed: J7.12, R239.2
unnamed: J7.10, R238.2
unnamed: J7.9, R237.2
unnamed: J2.19, R264.2
unnamed: J2.16, R263.2
unnamed: J2.15, R262.2
unnamed: J2.12, R261.2
unnamed: J3.19, R198.2
unnamed: J4.7, R181.2
unnamed: J4.6, R180.2
unnamed: J4.4, R179.2
unnamed: J4.3, R178.2
unnamed: J4.1, R177.2
unnamed: J4.9, R182.2
unnamed: J3.16, R197.2
unnamed: J3.15, R196.2
unnamed: J3.12, R195.2
unnamed: J3.10, R194.2
unnamed: J3.9, R193.2
unnamed: J7.7, R236.2
unnamed: J7.6, R235.2
unnamed: J7.4, R234.2
unnamed: J7.3, R233.2
unnamed: J7.1, R232.2
unnamed: J4.19, R187.2
unnamed: J4.16, R186.2
unnamed: J4.15, R185.2
unnamed: J4.12, R184.2
unnamed: J4.10, R183.2
unnamed: C45.1, U10.37
unnamed: C44.1, U8.37
unnamed: J7.18, R338.2
unnamed: C47.1, U11.37
unnamed: J3.1, R188.2
unnamed: J3.3, R189.2
unnamed: J3.4, R190.2
unnamed: J3.6, R191.2
unnamed: J3.7, R192.2
unnamed: J5.B2, R222.2
unnamed: J5.B23, R230.2
unnamed: J5.B10, R226.2
unnamed: J5.B9, R225.2
unnamed: J5.B7, R224.2
unnamed: J5.B6, R223.2
unnamed: J5.B1, R221.2
unnamed: J5.A18, R207.2
unnamed: J5.A17, R206.2
unnamed: J5.A16, R205.2
unnamed: J5.A24, R209.2
unnamed: J5.A23, R208.2
unnamed: J6.A9, R247.2
unnamed: J6.A18, R251.2
unnamed: J6.A17, R250.2
unnamed: J6.A16, R249.2
unnamed: J6.A24, R253.2
unnamed: J6.A23, R252.2
unnamed: J6.A10, R248.2
unnamed: J5.A10, R204.2
unnamed: J6.A7, R246.2
unnamed: J6.A6, R245.2
unnamed: J6.A2, R244.2
unnamed: J6.A1, R243.2
unnamed: J5.B18, R229.2
unnamed: J5.B17, R228.2
unnamed: J5.B16, R227.2
unnamed: J5.B24, R231.2
unnamed: J5.A9, R203.2
unnamed: J5.A7, R202.2
unnamed: J5.A6, R201.2
unnamed: J5.A2, R200.2
unnamed: J5.A1, R199.2
unnamed: J6.B1, R210.2
unnamed: J6.B6, R212.2
unnamed: J6.B23, R219.2
unnamed: J6.B18, R218.2
unnamed: J6.B17, R217.2
unnamed: J6.B16, R216.2
unnamed: J6.B10, R215.2
unnamed: J6.B9, R214.2
unnamed: J6.B7, R213.2
unnamed: J6.B24, R220.2
unnamed: J6.B2, R211.2
unnamed: P1.10, R358.1
unnamed: P1.8, R143.1
unnamed: Q1.3, R293.1
unnamed: J9.A14, R335.2
unnamed: J8.17, R351.2
unnamed: J8.19, R353.2
unnamed: J8.18, R352.2
unnamed: J8.16, R350.2
unnamed: C211.2, C212.2, R359.1, U24.2
unnamed: J8.52, R356.1
unnamed: J8.53, R357.1
unnamed: J8.51, R355.1
unnamed: J8.50, R354.1
unnamed: P1.4, R141.1
unnamed: P1.6, R142.1
unnamed: C201.1, U20.6
unnamed: C200.1, U20.4
unnamed: C183.2, U19.12
unnamed: C202.2, U20.7
unnamed: C201.2, U20.5
unnamed: C203.2, U20.3
unnamed: C200.2, U20.2
unnamed: P51.4, R360.1
unnamed: D37.1, R339.1
unnamed: D38.1, R340.1
unnamed: D39.1, R341.1
VCC1V2: C49.1, C52.1, C55.1, C58.1, C61.1, C64.1, C67.1, C70.1, C73.1, C76.1, C79.1, C82.1, C84.1, C87.1, C90.1, C93.1, C96.1, C99.1, C102.1, C104.1, C106.1, R130.1, R131.1, R155.2, R157.2, R327.2, U12.A5, U12.A13, U12.B11, U12.C8, U12.D6, U12.D12, U12.E11, U12.G7, U12.H9, U12.H11, U12.J8, U12.J10, U12.K9, U12.K11, U12.L8, U12.L10, U12.M7, U12.M12, U18.5
VCC3V3: C1.1, C2.1, C3.1, C4.1, C5.1, C6.1, C9.1, C10.1, C12.1, C48.1, C50.1, C53.1, C54.1, C56.1, C59.1, C60.1, C62.1, C65.1, C66.1, C68.1, C69.1, C71.1, C74.1, C77.1, C80.1, C83.1, C85.1, C88.1, C91.1, C94.1, C97.1, C100.1, C103.1, C105.1, C107.1, C108.1, C110.1, C139.2, C173.1, C174.1, C175.1, C178.1, C179.1, C180.1, C181.1, C182.1, C194.1, C195.1, C196.1, C197.1, C198.1, C199.1, D2.1, P1.2, P48.2, R1.1, R2.1, R3.1, R19.1, R20.1, R23.2, R24.1, R28.2, R30.2, R31.1, R32.2, R34.2, R57.1, R58.2, R59.1, R60.2, R61.1, R62.2, R63.1, R64.2, R65.1, R66.1, R67.1, R68.1, R69.1, R73.1, R77.1, R79.2, R80.1, R81.2, R83.2, R85.2, R86.2, R87.2, R88.2, R89.2, R90.1, R91.1, R92.1, R95.1, R96.1, R97.1, R98.1, R99.1, R111.1, R114.2, R116.2, R128.1, R129.1, R133.1, R144.2, R146.2, R147.2, R148.2, R150.2, R152.2, R154.2, R166.2, R168.2, R266.2, R290.2, R294.2, R295.2, R300.1, R301.2, R302.1, R303.2, R304.2, R305.1, R306.2, R314.2, R315.1, R316.2, R317.1, R320.2, R321.1, R322.2, R326.2, R339.2, R340.2, R341.2, R350.1, R353.1, R354.2, R357.2, R367.1, R368.2, R369.2, U1.3, U1.7, U1.11, U1.17, U1.27, U1.32, U1.43, U1.55, U2.8, U6.7, U6.10, U8.2, U9.2, U10.2, U11.2, U12.B1, U12.B15, U12.B17, U12.E14, U12.E17, U12.F8, U12.G10, U12.G15, U12.J12, U12.J14, U12.J17, U12.K7, U12.M9, U12.M15, U12.P5, U12.P9, U12.P10, U12.P14, U12.R6, U12.R12, U12.R17, U12.U4, U12.U9, U12.U14, U13.1, U13.4, U17.8, U18.2, U18.4, U19.23, U19.24, U19.25, U19.32, U19.48, U19.71, U20.15, U20.16, U21.1
VCC5V0: C207.1, C209.1, C211.1, R70.1, R71.1, R72.1, R74.1, R75.1, R76.1, R93.1, R94.1, R117.1, R118.1, R123.1, R293.2, R342.1, R343.1, R351.1, R352.1, R355.2, R356.2, U8.1, U9.1, U10.1, U11.1, U18.9, U22.3, U23.3, U24.3
VCC12V0: C17.1, C18.2, C19.2, C20.1, C22.1, C115.2, C116.1, C117.2, C119.1, C120.2, C121.2, C122.1, C125.2, C128.2, C129.2, C130.2, C131.1, C134.2, C135.2, C137.2, R35.1, R39.1, R42.1, R119.1, R121.1, R122.1, R267.1, R328.1, U3.13, U3.14, U4.13, U4.14, U5.13, U5.14, U14.12, U14.13, U14.14, U14.15, U14.16, U14.17, U14.19, U18.13

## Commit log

2015-07-19 Issue#330 - Create initial repository for the HDMI2USB board.
2015-07-19 Issue #319
2015-07-19 Issue #325
2015-07-19 Issue #331 - Importing initial third_party parts.
2015-07-19 Issue #336
2015-07-19 Issue #352 - Adding rough (but to scale) mechanical diagram of front panel.
2015-07-19 Issue #344
2015-07-19 Issue #363 - Making the path to libraries to be relative.
2015-07-19 Issue #346
2015-07-19 Issue #362: Adding ignore for credentials.
2015-07-19 Issue #362: Generate the lookup name in Python.
2015-07-19 Issue #362: Python script for uploading KiCad NetList into our spreadsheet.
2015-07-19 Issue #412
2015-07-19 Issue #510 - DDR routing just completed
2015-07-19 Issue #337
2015-07-19 Issue #510
2015-07-19 Issue #412 - Placement
2015-07-19 Issue #510 - DDR routing
2015-07-19 Issue #510 - Fanout of Spartan6
2015-07-19 Issue #510 - DDR Routing dome by manu
2015-07-19 Issue #510 - Length Matching completed in the following sections D0-D15, CKE,CK_P,CK_N,LDM,UDM,LDQS_N,UDQS_N,LDQS_P,UDQS_P,WE. length matched between 31.6 to 31.8 mm.
2015-07-19 Issue #667 - hdmi 2 usb board review report.
2015-07-19 Issue #510 - Length Matching Started.
2015-07-19 Issue #510 - Length Matching completed
2015-07-19 Issue #705 - HDMI and DVI routing
2015-07-19 Issue #510 - Resolving issues which is in the spread sheet.
2015-07-19 Issue #606 - Length Matching.
2015-07-19 Issue #606 - Signal 1 is completed.
2015-07-19 Issue #606 - Adding test points
2015-07-19 Issue #859 - HDMI routing.
2015-07-19 Issue #606 - Length matching od DDR signals are finished.
2015-07-19 Issue #859 - Changes as per the review DDR section review and HDMI routing.
2015-07-19 Issue #859 - Changes as per the review
2015-07-19 Issue #606
2015-07-19 Issue #859 - HDMI buffer routing.
2015-07-19 Issue #859 - hdmi BUFFER ROUTING COMPLETED.
2015-07-19 Issue #859 - HDMI routing
2015-07-19 Issue #859 - U10 and U11 completed.
2015-07-19 Issue #859 - Resolving the length issue
2015-07-19 Issue #958 - Power supply schematic completed
2015-07-19 Issue #921 - vhdci routing
2015-07-19 Issue #958 - Adding power supply for hdmi2usb
2015-07-19 Issue #921 - GTP routing
2015-07-19 Issue #934 - GTP routing
2015-07-19 Issue #934 - Power supply
2015-07-19 Issue #1022 - Power supply
2015-07-19 Issue #1007: Updating upload-netlist to batch requests for pin updates.
2015-07-19 Issue #1022 - Power supply & pic& SCHEMATIC SECTION.
2015-07-19 Issue #1022 - Power supply & pic
2015-07-19 Issue #1022 - Cypress
2015-07-19 Issue #1022 - Reset signals
2015-07-19 Issue #1022 - Schematics final.
2015-07-19 Issue #1022 - RS232,RS422
2015-07-19 Issue #1022 - Cypress usb
2015-07-19 Issue #1027 - Schematics final changes.
2015-07-19 Issue #1007: Small unicode fixes, plus less verbose output for upload-netlist.py
2015-07-19 Issue #1022 - Schematics final changes.
2015-07-19 Issue #1049 - Termination resisters in GTP lines
2015-07-19 Issue #993
2015-07-19 Issue #1053 - Cypress routing
2015-07-19 Issue #1050
2015-07-19 Issue #1082 - DRC clearing
2015-07-19 Issue #1083 - Adding optimizations.
2015-07-19 Issue #1056 - Copper pouring.
2015-07-19 Issue #1084 - Copper pouring.
2015-07-19 Issue #1084 - Making all the mounting holes ground
2015-07-19 Issue #1084 - Final changes in the LED header p51
2015-07-19 Issue #1103: Fixing case of DVI-stacked.
2015-07-19 Issue #1084 - CHANGES IN THE SILK SCREEN
2015-07-19 Issue #362: Adding requirements.txt for the upload script.
2015-07-19 Issue #1103: Fixing for case sensitivity.
2015-07-19 Issue #1084 - Final CHANGES IN THE SILK SCREEN
2015-07-19 Issue #1084 - VHDCI footprint outer dimension changed, silk screen changes,
2015-07-19 Issue #1084 - Changes in revision
2015-07-19 Issue #1084 - Added LED silk screen. Added copper pouring in signal layer.
2015-07-19 Issue #1084 - Changes in outer line.
2015-07-19 Issue #1084 - Changes in per layer
2015-07-19 Issue #1084 - Changes in pwr layer
2015-07-19 Issue #1084 - Almost every changes made as per the mail details.
2015-07-19 Issue #1084 - Moving USB connector.
2015-07-19 Issue #1084 - Final Changes Made on the silks.
2015-07-19 Issue #1084 - Final copper pouring
2015-07-19 Issue #1084 - DC jack reference not found so added new reference as K2,K3.
2015-07-19 Issue #1084 - Found text "OUT 1V8" in the bottom side of the resister. Corrected
2015-07-19 Issue #1084 - Dvi Pin out direction is changed.
2015-07-19 Issue #1128 - Rectifier foot print drill size changed.
2015-07-19 Issue #1129 - Gerber and final board file in tags
2015-07-19 Issue #1135 - LED board for HDMI
2015-07-19 Issue #1117 - LED board for HDMI
2015-07-19 Add snapshots of documentation.
2015-07-19 Adding information about the status of this branch.
2015-07-19 Starting again with different design and new name 'Opsis'.
    The Numato Opsis makes a number of different decisions to the first attempt at
    doing a HDMI2USB production board.
2015-07-19 Issue #1458 - Adding New schematics
2015-07-19 Issue #1458 - HDMI RX TX pins added, Cypress added, DDR added
2015-07-19 Issue #1458 - USB2.0
2015-07-19 Issue #1480
2015-07-19 Issue #1471 - Changes in Cypress
2015-07-19 Issue #1471 - USB schematic changes
2015-07-19 Issue #1470 - HDMI Sheet changes
2015-07-19 Issue #1471 - usb Sheet changes
2015-07-19 Issue #1470 - Removing Cypress.sch
2015-07-19 Issue #1471 - HDMI Sheet changes
2015-07-19 Issue #1546 - Adding an TimVideos PCIe 8x to Digilent Atlys VHDCI adapter.
    Also fixes Issue #1543.
2015-07-19 Issue #1583 - Fixing up library paths in .pro file.
2015-07-19 Issue #1583 - Adding the expansion library too.
2015-07-19 Issue #1583 - Rename expansion/lbr to expansion/libraries to be consistent.
2015-07-19 Issue #1481 - DOC
2015-07-19 Issue #1583 - Copying hdmi2usb library into rev2 board.
2015-07-19 Issue #1473 - Fixing UTMI schematic and adding text descriptions.
2015-07-19 Issue #1481 - Placement
2015-07-19 Issue #1412 - Placement
2015-07-19 Issue #1481 - CYPRESS-FPGA CONNECTIONS ADDED
2015-07-19 Issue #1481 - GPIO sheet
2015-07-19 Issue #1605 - Cypress routing
2015-07-19 Issue #1412 - Placement on 6-3-15
2015-07-19 Issue #1608 - Placement
2015-07-19 Issue #1680 - Bank 0 Ios
2015-07-19 Issue #1488 - Added diode display port power pin
2015-07-19 Issue #1708 - Placement
2015-07-19 Issue #1683
2015-07-19 Issue #1605
2015-07-19 Issue #1670
2015-07-19 Issue #1585
2015-07-19 Issue #1647 - Final changes
2015-07-19 Issue #1585 - Fixing the library paths.
2015-07-19 Issue #1713
2015-07-19 Issue #1546
2015-07-19 Issue #1767 - Feedback changes
2015-07-19 Issue #1786 - Final Changes
2015-07-19 Issue #1739
2015-07-19 Issue #1601 - USB micro footprint
2015-07-19 Issue #1804 - Adding RX/TX direction fields.
2015-07-19 Issue #1799 - Feedback changes
2015-07-19 Issue #1849 - Gerber files
2015-07-19 Issue #1804 - Fixing RX/TX direction fields.
2015-07-19 Issue #1851 - UCF
2015-07-19 Issue #1961 - Adding initial "populate" field to all components.
2015-07-19 Issue #1961 - Making the population instructions hidden.
2015-07-19 Issue #1950 - Adding DisplayPort DC blocking capacitors to schematic.
2015-07-19 Issue #1961 - Marking parts as "don't populate".
    * Conference power supply.
    * Debugging GTP clocks.
2015-07-19 Adding more information to the README file.
2015-07-19 Adding information about the KiCad version used.
2015-07-19 Adding a picture of the board.
2015-07-23 Importing footprint names into schematic.
2015-07-23 Fixing the power field.
2015-08-25 Making the do-not-populate information clearer.
2015-08-26 s/VTTREF0/VTTREF/
    https://github.com/timvideos/HDMI2USB-numato-opsis-hardware/issues/12
2015-08-26 Updating netlist file.
2015-08-26 Adding test points to CEC and HPD lines.
    https://github.com/timvideos/HDMI2USB-numato-opsis-hardware/issues/17
2015-08-26 Fixing up GND references in the HDMI sheet.
    https://github.com/timvideos/HDMI2USB-numato-opsis-hardware/issues/19
2015-08-26 Fixing DRC errors.
2015-08-26 Adding a .gitignore file.
2015-08-26 Removing R151,R204
    https://github.com/timvideos/HDMI2USB-numato-opsis-hardware/issues/16
2015-08-26 Fixing values of R141,R142,R197,R196
    https://github.com/timvideos/HDMI2USB-numato-opsis-hardware/issues/16
2015-08-26 Replace www.hdmi2usb.tv with hdmi2usb.tv
    Fixes #10
    https://github.com/timvideos/HDMI2USB-numato-opsis-hardware/issues/10
2015-08-26 Fixing the grouping of the HDMI signals.
    Fixes #22
    https://github.com/timvideos/HDMI2USB-numato-opsis-hardware/issues/22
2015-08-26 Fix the signal name changing.
    Fixes #23.
    https://github.com/timvideos/HDMI2USB-numato-opsis-hardware/issues/23
2015-08-26 Fixing the Cypress UART ordering.
    This shouldn't change anything in the PCB layout.
    Fixes #13
    https://github.com/timvideos/HDMI2USB-numato-opsis-hardware/issues/13
2015-08-26 KiCad is deciding to renumber the GND parts.
2015-08-26 Adding silkscreen for debug IO header.
    Fixes #11.
    https://github.com/timvideos/HDMI2USB-numato-opsis-hardware/issues/11
2015-08-26 Updating .net and .cmp file.
2015-08-31 Replace 0402 with SM0402.
2015-09-04 Adding CrowdSupply campaign to README.md
2015-09-13 Adding CrowdSupply image badge.
2015-09-14 Issue #9
    Added DC blocking capacitors, VTTREF issue solved, 5V power common
    connection issue solved
2015-10-20 Changes on 2015-10-21@7-21PM
2015-11-02 Changes on 12-11-2015 Micro SD header added.#35
2015-11-03 #29 Issue
2015-11-03 Added some more GND vias
2015-11-03 Adding extra mounting holes for Issue #18.
    Fixes #18.
2015-11-07 s/mfd/uF/gci
2015-11-07 s/UF/uF/gc
2015-11-07 s/NF/nF/gc
2015-11-07 s/PF/pF/gc
2015-11-07 s/_Capa//gc
2015-11-07 s/_Resistor//gc
2015-11-07 s/0402/SM0402/gc
2015-11-07 s/1uF/1.0uF/gc
2015-11-07 s/uFD/uF/gc
2015-11-10 Final changes
2015-11-10 Final Gerber
2016-01-04 Fixing issue with clock labeling.
    Fixes #42.
2016-01-11 Improving the comments in the schematic.
2016-01-11 Embedding the Git SHA into the schematic files.
2016-01-11 Small formatting fixes.
2016-01-11 Adding PDF version of the schematic.
2016-04-26 Adding a cases directory with README.
2016-04-26 Small fix to cases README.
2016-06-13 Added front.svg, containing vector outlines of the front ports
2016-06-14 Added STL files for 'thin' shield
2016-06-14 Update filenames in README
2016-07-25 Added STL files for full size ATX shield.
2016-07-25 Adding TODO info.
2016-07-25 Adding standoff information.
2016-07-25 Adding Thingiverse link.
2017-07-28 Fixing 3d models for lots of parts.
2017-08-12 Working on upgrading schematic to latest KiCad.
2017-08-12 Removing special library.
2017-08-13 Renaming files to better match actual name.
2017-08-13 Rename things.
2017-08-13 More renames.
2017-08-13 Rename library.
2017-08-13 Fixing libraries a little.
2017-08-13 Why are things changing!?
2017-09-20 Create README in the img directory.
2018-04-27 Link to current Opsis supplier page
